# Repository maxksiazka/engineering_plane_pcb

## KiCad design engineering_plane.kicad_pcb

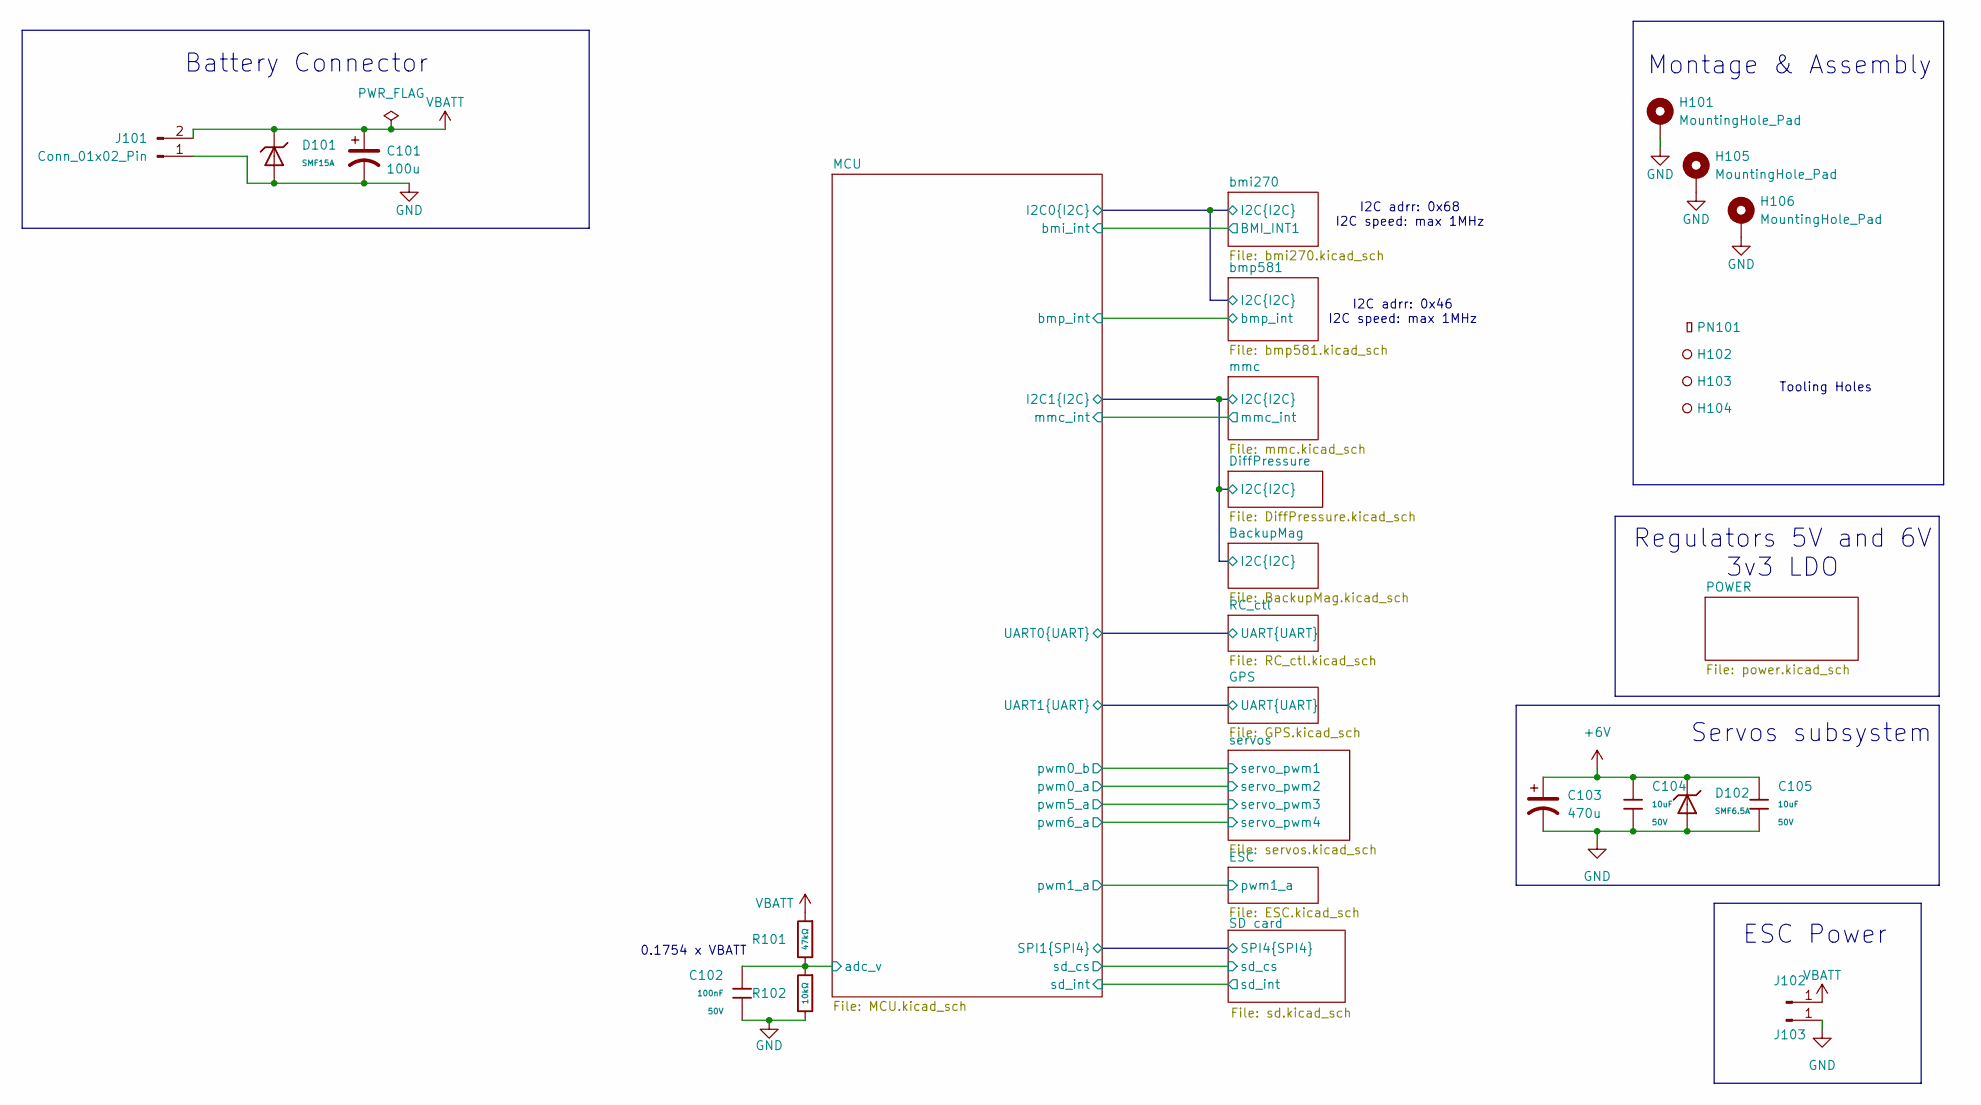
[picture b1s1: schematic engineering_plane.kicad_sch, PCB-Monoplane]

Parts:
C101: 100u; CP_Elec_6.3x7.7; Voltage 1kV; Tolerance 100%
C102: 100nF; C_0402; Voltage Rated 50V; Tolerance ±10%; Part CL05B104KB54PNC; LCSC C307331
C103: 470u; CP_Elec_10x10.5; Voltage 1kV; Tolerance 100%
C104, C105: 10uF; C_1206; Voltage Rated 50V; Tolerance ±10%; Part CL31A106KBHNNNE; LCSC C13585
D101: SMF15A; D_SOD-123FL; Clamping Voltage 24.4V; Voltage - Breakdown 16.7V; Part SMF15A; LCSC C19077509
D102: SMF6.5A; D_SOD-123FL; Clamping Voltage 11.2V; Voltage - Breakdown 7.98V; Part SMF6.5A; LCSC C41376089
H101, H105, H106: MountingHole_Pad; MountingHole_3.2mm_M3_Pad
H102, H103, H104: Hole_Tooling_JLCPCB
J101: Conn_01x02_Pin; AMASS_XT30PW-M_1x02_P2.50mm_Horizontal
J102, J103: Conn_01x01_Pin; SolderWire-2sqmm_1x01_D2mm_OD3.9mm
PN101: Part_Num_JLCPCB
R101: 47kΩ; R_0402; Overload Voltage (Max) 50V; Tolerance ±1%; Part 0402WGF4702TCE; LCSC C25792
R102: 10kΩ; R_0402; Overload Voltage (Max) 50V; Tolerance ±1%; Part 0402WGF1002TCE; LCSC C25744

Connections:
+6V: C103.1, C104.1, C105.1, D102.1; also elsewhere on the board
/MCU/adc_v: C102.1, R101.2, R102.1; also elsewhere on the board
GND: C101.2, C102.2, C103.2, C104.2, C105.2, D101.2, D102.2, H101.1 (1_1), H105.1 (1_1), H106.1 (1_1), J101.1, J103.1 (Pin_1_1), R102.2; also elsewhere on the board
VBATT: C101.1, D101.1, J101.2, J102.1 (Pin_1_1), R101.1; also elsewhere on the board

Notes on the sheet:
ESC Power
I2C adrr: 0x46 I2C speed: max 1MHz
Regulators 5V and 6V 3v3 LDO
0.1754 x VBATT
Tooling Holes
I2C adrr: 0x68 I2C speed: max 1MHz
Battery Connector
Montage & Assembly
Servos subsystem

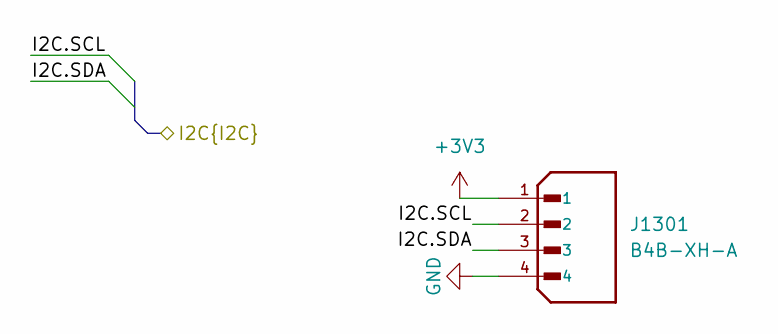
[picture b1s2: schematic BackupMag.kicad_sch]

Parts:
J1301: B4B-XH-A; JST_B4B-XH-A; PARTREV 7/4/21

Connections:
+3V3: J1301.1; also elsewhere on the board
/BackupMag/I2C.SCL: J1301.2; also elsewhere on the board
/BackupMag/I2C.SDA: J1301.3; also elsewhere on the board
GND: J1301.4; also elsewhere on the board

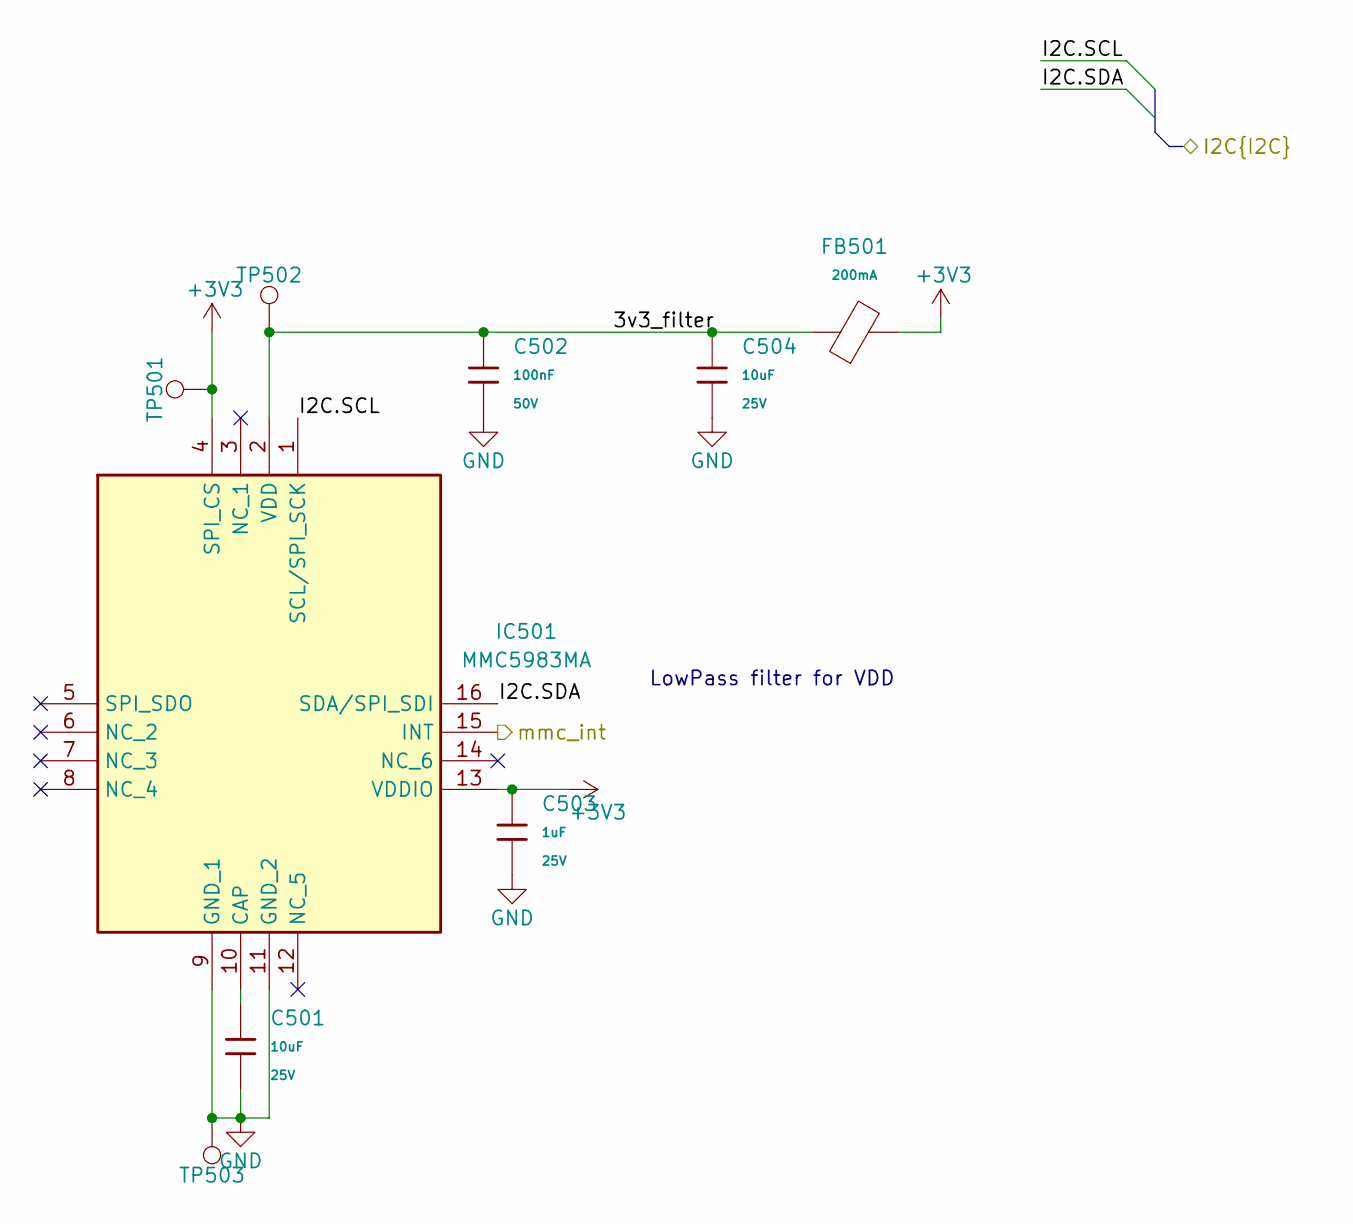
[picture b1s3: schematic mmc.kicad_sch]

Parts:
C501, C504: 10uF; C_0603; Voltage Rated 25V; Tolerance ±20%; Part CL10A106MA8NRNC; LCSC C96446
C502: 100nF; C_0402; Voltage Rated 50V; Tolerance ±10%; Part CL05B104KB54PNC; LCSC C307331
C503: 1uF; C_0402; Voltage Rated 25V; Tolerance ±10%; Part CL05A105KA5NQNC; LCSC C52923
FB501: FB_0603; Current Rating 200mA; Tolerance ±25%; Part GZ1608D601TF; LCSC C1002
IC501: MMC5983MA; Mouser Part Number 438-MMC5983MA
TP501, TP502, TP503: 1.0mm; TestPoint-1.0mm

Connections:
+3V3: C503.1, FB501.2, IC501.4 (SPI_CS), IC501.13 (VDDIO), TP501.1 (1_1); also elsewhere on the board
/BackupMag/I2C.SCL: IC501.1 (SCL/SPI_SCK); also elsewhere on the board
/BackupMag/I2C.SDA: IC501.16 (SDA/SPI_SDI); also elsewhere on the board
/MCU/mmc_int: IC501.15 (INT); also elsewhere on the board
/mmc/3v3_filter: C502.1, C504.1, FB501.1, IC501.2 (VDD), TP502.1 (1_1)
GND: C501.2, C502.2, C503.2, C504.2, IC501.9 (GND_1), IC501.11 (GND_2), TP503.1 (1_1); also elsewhere on the board
unnamed: C501.1, IC501.10 (CAP)

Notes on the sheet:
LowPass filter for VDD

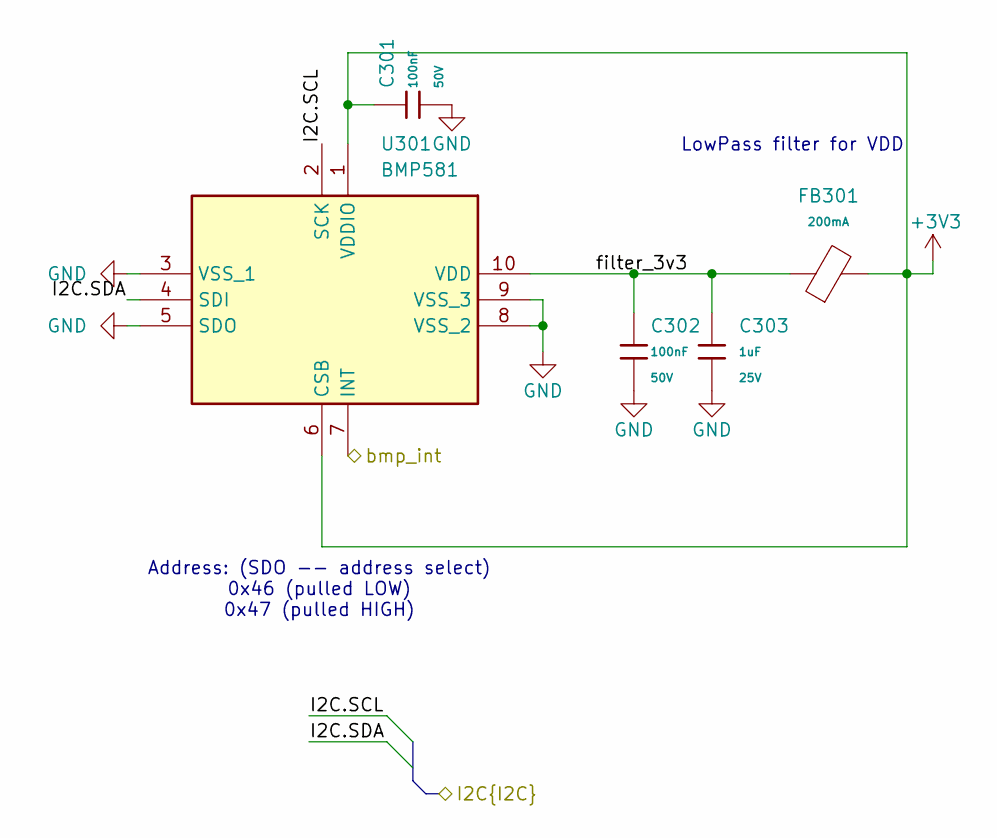
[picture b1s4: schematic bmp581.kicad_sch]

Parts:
C301, C302: 100nF; C_0402; Voltage Rated 50V; Tolerance ±10%; Part CL05B104KB54PNC; LCSC C307331
C303: 1uF; C_0402; Voltage Rated 25V; Tolerance ±10%; Part CL05A105KA5NQNC; LCSC C52923
FB301: FB_0603; Current Rating 200mA; Tolerance ±25%; Part GZ1608D601TF; LCSC C1002
U301: BMP581; Mouser Part Number 262-BMP581

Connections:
+3V3: C301.1, FB301.2, U301.1 (VDDIO), U301.6 (CSB); also elsewhere on the board
/MCU/I2C0.SCL: U301.2 (SCK); also elsewhere on the board
/MCU/I2C0.SDA: U301.4 (SDI); also elsewhere on the board
/MCU/bmp_int: U301.7 (INT); also elsewhere on the board
/bmp581/filter_3v3: C302.1, C303.1, FB301.1, U301.10 (VDD)
GND: C301.2, C302.2, C303.2, U301.3 (VSS_1), U301.5 (SDO), U301.8 (VSS_2), U301.9 (VSS_3); also elsewhere on the board

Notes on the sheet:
Address: (SDO -- address select) 0x46 (pulled LOW) 0x47 (pulled HIGH)
LowPass filter for VDD

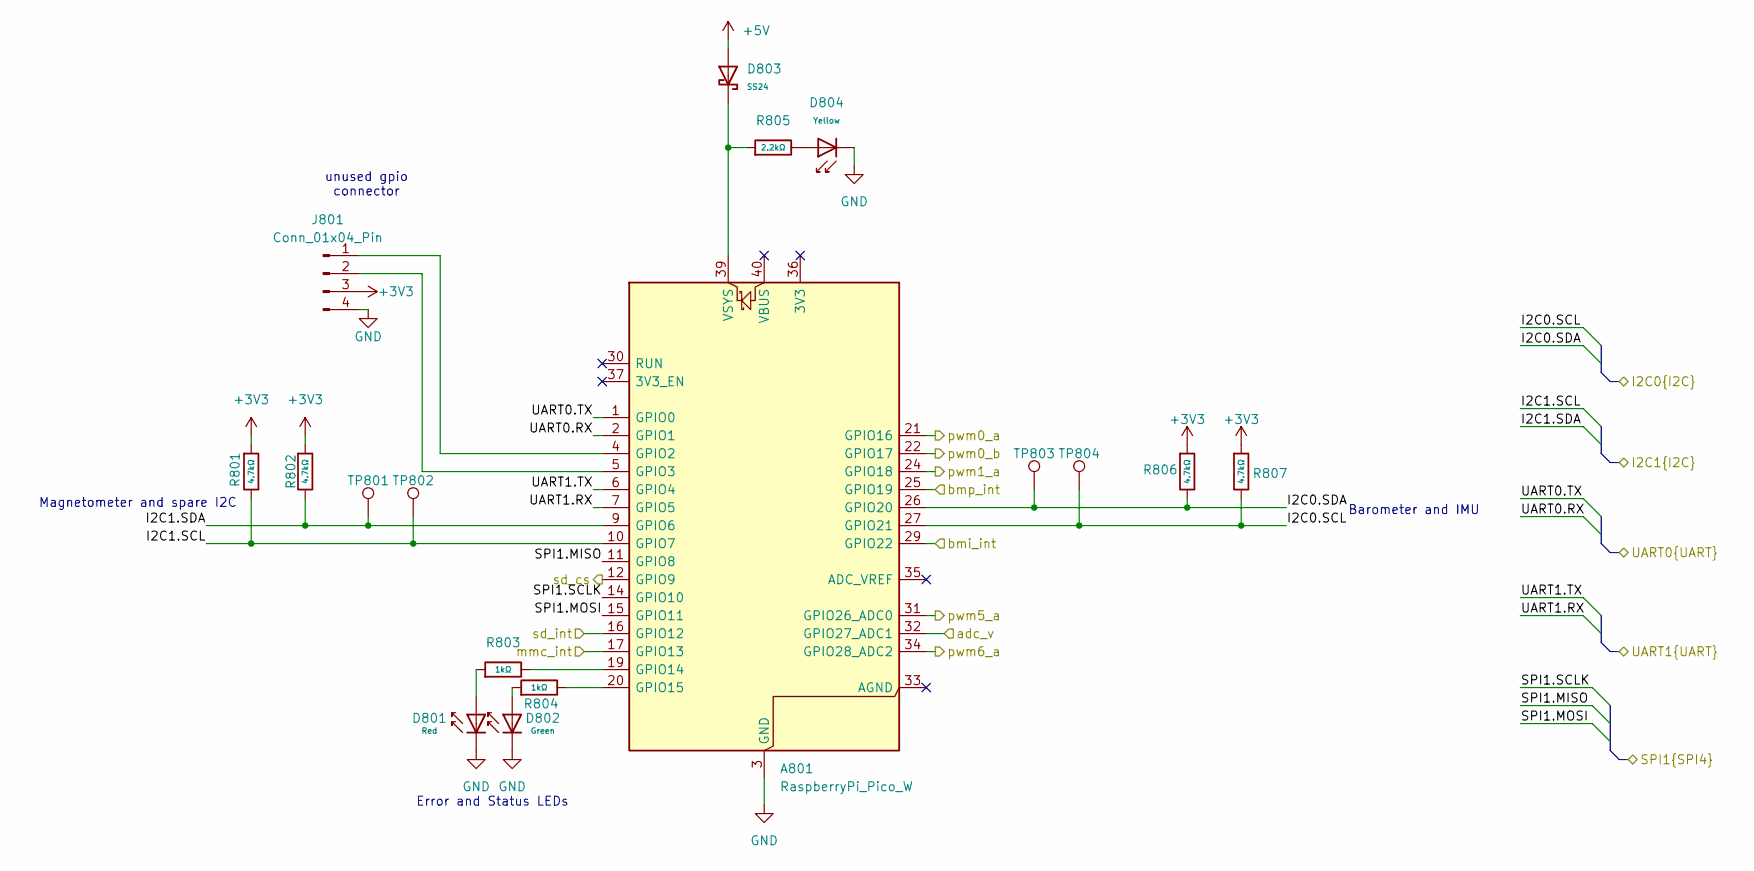
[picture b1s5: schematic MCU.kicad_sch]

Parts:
A801: RaspberryPi_Pico_W; RaspberryPi_Pico_Common_SMD
D801: Red; D_0805; Forward Voltage (VF) 1.6V~2.6V; Part NCD0805R1; LCSC C84256
D802: Green; D_0805; Part KT-0805G; LCSC C2297
D803: SS24; D_SMA; Forward Voltage (Vf@If) 0.55V@1.0A; Reverse Voltage (Vr) 40V; Part SS24; LCSC C7420362
D804: Yellow; D_0603; Forward Voltage (VF) 1.6V~2.6V; Part NCD0603Y2; LCSC C89811
J801: Conn_01x04_Pin; PinHeader_1x04_P2.54mm_Vertical
R801, R802, R806, R807: 4.7kΩ; R_0402; Overload Voltage (Max) 50V; Tolerance ±1%; Part 0402WGF4701TCE; LCSC C25900
R803, R804: 1kΩ; R_0402; Overload Voltage (Max) 50V; Tolerance ±1%; Part 0402WGF1001TCE; LCSC C11702
R805: 2.2kΩ; R_0402; Overload Voltage (Max) 50V; Tolerance ±1%; Part 0402WGF2201TCE; LCSC C25879
TP801, TP802, TP803, TP804: 1.0mm; TestPoint-1.0mm

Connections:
+3V3: J801.3, R801.1, R802.1, R806.1, R807.1; also elsewhere on the board
+5V: D803.2; also elsewhere on the board
/BackupMag/I2C.SCL: A801.10 (GPIO7), R801.2, TP802.1 (1_1); also elsewhere on the board
/BackupMag/I2C.SDA: A801.9 (GPIO6), R802.2, TP801.1 (1_1); also elsewhere on the board
/ESC/pwm1_a: A801.24 (GPIO18); also elsewhere on the board
/GPS/UART.RX: A801.7 (GPIO5); also elsewhere on the board
/GPS/UART.TX: A801.6 (GPIO4); also elsewhere on the board
/MCU/I2C0.SCL: A801.27 (GPIO21), R807.2, TP804.1 (1_1); also elsewhere on the board
/MCU/I2C0.SDA: A801.26 (GPIO20), R806.2, TP803.1 (1_1); also elsewhere on the board
/MCU/SPI1.MISO: A801.11 (GPIO8); also elsewhere on the board
/MCU/SPI1.MOSI: A801.15 (GPIO11); also elsewhere on the board
/MCU/SPI1.SCLK: A801.14 (GPIO10); also elsewhere on the board
/MCU/UART0.RX: A801.2 (GPIO1); also elsewhere on the board
/MCU/UART0.TX: A801.1 (GPIO0); also elsewhere on the board
/MCU/adc_v: A801.32 (GPIO27_ADC1); also elsewhere on the board
/MCU/bmi_int: A801.29 (GPIO22); also elsewhere on the board
/MCU/bmp_int: A801.25 (GPIO19); also elsewhere on the board
/MCU/mmc_int: A801.17 (GPIO13); also elsewhere on the board
/MCU/pwm0_a: A801.21 (GPIO16); also elsewhere on the board
/MCU/pwm0_b: A801.22 (GPIO17); also elsewhere on the board
/MCU/pwm5_a: A801.31 (GPIO26_ADC0); also elsewhere on the board
/MCU/pwm6_a: A801.34 (GPIO28_ADC2); also elsewhere on the board
/MCU/sd_cs: A801.12 (GPIO9); also elsewhere on the board
/MCU/sd_int: A801.16 (GPIO12); also elsewhere on the board
GND: A801.3 (GND), A801.8 (GND), A801.13 (GND), A801.18 (GND), A801.23 (GND), A801.28 (GND), A801.38 (GND), D801.1, D802.1, D804.1, J801.4; also elsewhere on the board
unnamed: A801.4 (GPIO2), J801.1
unnamed: A801.5 (GPIO3), J801.2
unnamed: A801.19 (GPIO14), R803.2
unnamed: A801.20 (GPIO15), R804.2
unnamed: A801.39 (VSYS), D803.1, R805.1
unnamed: D801.2, R803.1
unnamed: D802.2, R804.1
unnamed: D804.2, R805.2

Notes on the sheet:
Error and Status LEDs
Magnetometer and spare I2C
unused gpio connector
Barometer and IMU

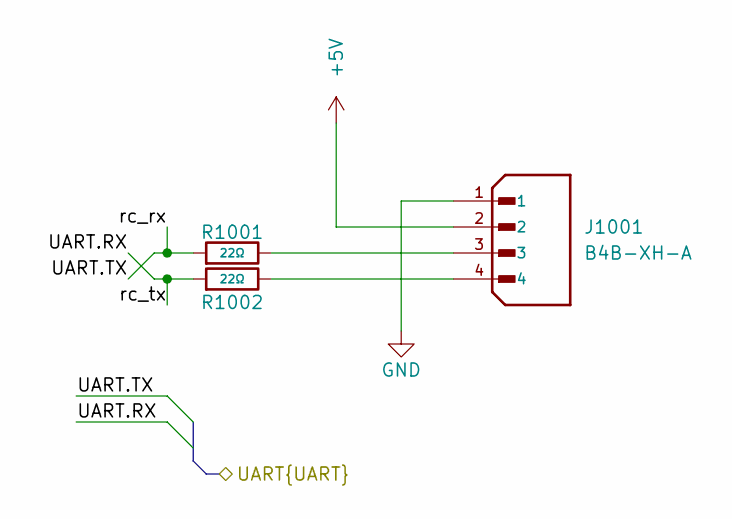
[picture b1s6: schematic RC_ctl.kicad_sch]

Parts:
J1001: B4B-XH-A; JST_B4B-XH-A; PARTREV 7/4/21
R1001, R1002: 22Ω; R_0603; Overload Voltage (Max) 75V; Tolerance ±1%; Part 0603WAF220JT5E; LCSC C23345

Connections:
+5V: J1001.2; also elsewhere on the board
/MCU/UART0.RX: R1002.1; also elsewhere on the board
/MCU/UART0.TX: R1001.1; also elsewhere on the board
GND: J1001.1; also elsewhere on the board
unnamed: J1001.3, R1001.2
unnamed: J1001.4, R1002.2

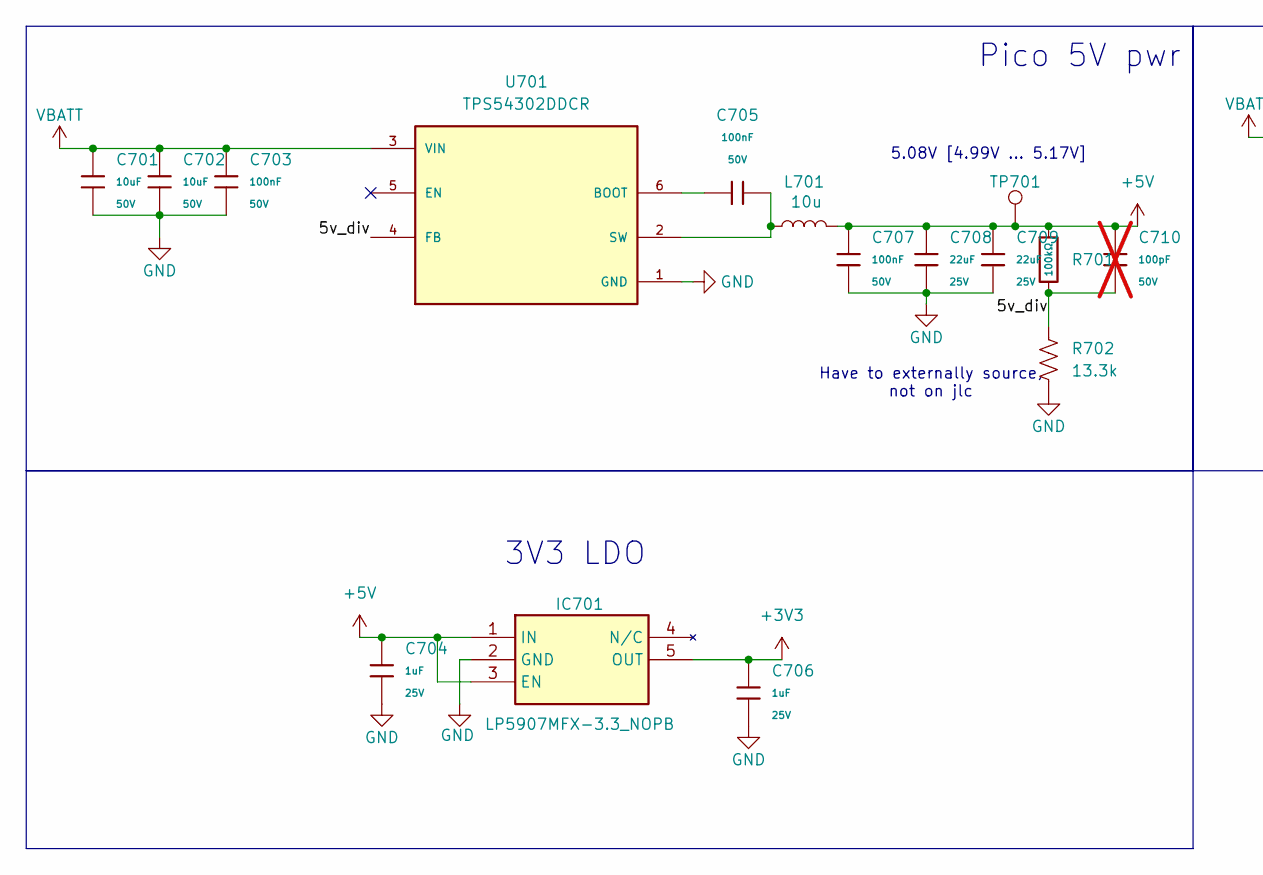
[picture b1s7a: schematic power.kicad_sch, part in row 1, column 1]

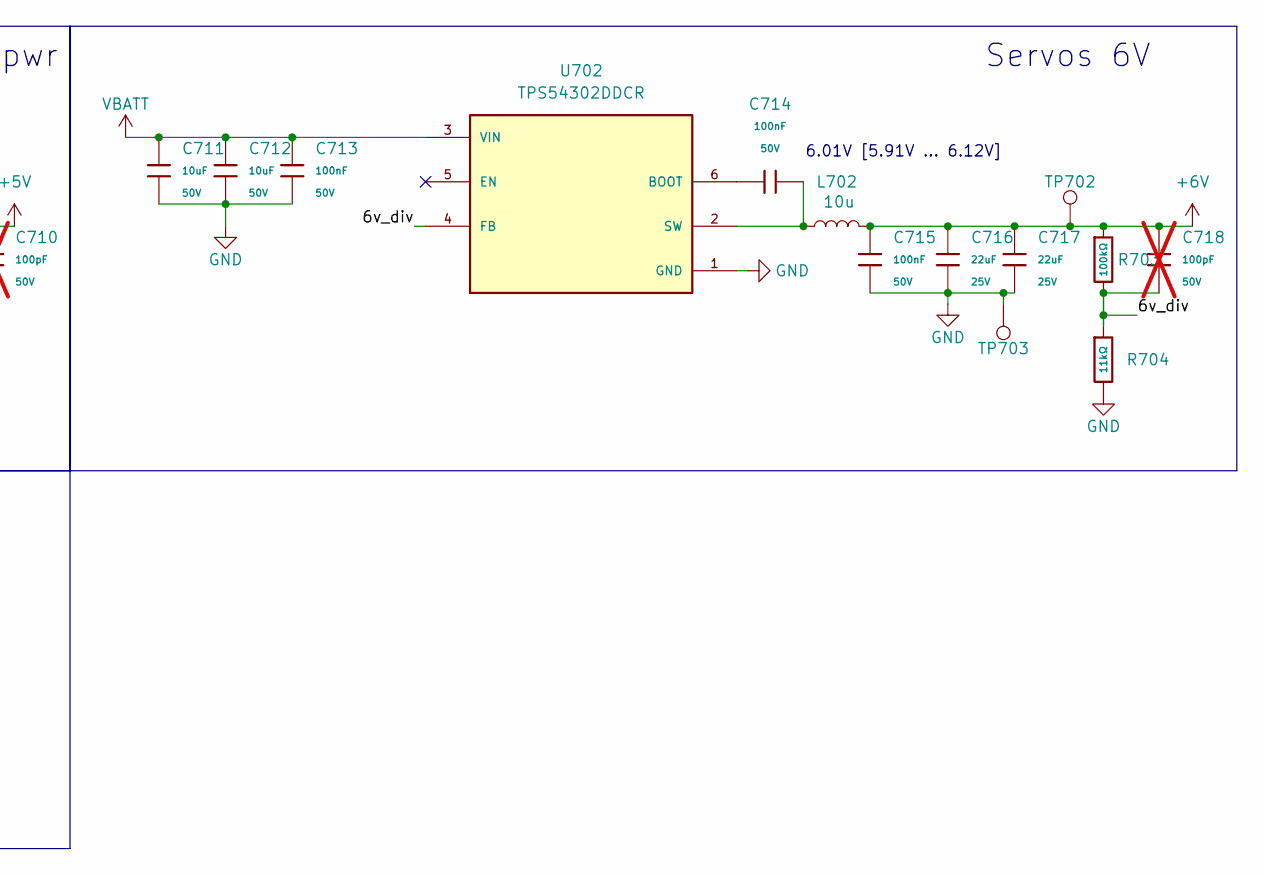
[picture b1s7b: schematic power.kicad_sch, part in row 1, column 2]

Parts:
C701, C702, C711, C712: 10uF; C_1206; Voltage Rated 50V; Tolerance ±10%; Part CL31A106KBHNNNE; LCSC C13585
C703, C705, C707, C713, C715: 100nF; C_0603; Voltage Rated 50V; Tolerance ±10%; Part CC0603KRX7R9BB104; LCSC C14663
C704, C706: 1uF; C_0402; Voltage Rated 25V; Tolerance ±10%; Part CL05A105KA5NQNC; LCSC C52923
C708, C709, C716, C717: 22uF; C_1206; Voltage Rated 25V; Tolerance ±10%; Part CL31A226KAHNNNE; LCSC C12891
C710, C718: 100pF; C_0603; Voltage Rated 50V; Tolerance ±5%; Part CL10C101JB8NNNC; LCSC C14858; not fitted
C714: 100nF; C_0402; Voltage Rated 50V; Tolerance ±10%; Part CL05B104KB54PNC; LCSC C307331
IC701: LP5907MFX-3.3_NOPB; SOT95P280X145-5M; Mouser Part Number 595-LP5907MFX-3.3NPB
L701: 10u; L_7.3x7.3_H4.5
L702: 10u; 7447714220
R701, R703: 100kΩ; R_0603; Overload Voltage (Max) 75V; Tolerance ±1%; Part 0603WAF1003T5E; LCSC C25803
R702: 13.3k; R_0603_1608Metric
R704: 11kΩ; R_0603; Overload Voltage (Max) 75V; Tolerance ±1%; Part 0603WAF1102T5E; LCSC C25950
TP701, TP702, TP703: 1.0mm; TestPoint-1.0mm
U701, U702: TPS54302DDCR; SOT95P280X110-6N; PARTREV A

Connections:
+3V3: C706.1, IC701.5 (OUT); also elsewhere on the board
+5V: C704.1, C707.1, C708.1, C709.1, C710.1, IC701.1 (IN), IC701.3 (EN), L701.2, R701.1, TP701.1 (1_1); also elsewhere on the board
+6V: C715.1, C716.1, C717.1, C718.1, L702.2, R703.1, TP702.1 (1_1); also elsewhere on the board
/POWER/5v_div: C710.2, R701.2, R702.2, U701.4 (FB)
/POWER/6v_div: C718.2, R703.2, R704.1, U702.4 (FB)
GND: C701.2, C702.2, C703.2, C704.2, C706.2, C707.2, C708.2, C709.2, C711.2, C712.2, C713.2, C715.2, C716.2, C717.2, IC701.2 (GND), R702.1, R704.2, TP703.1 (1_1), U701.1 (GND), U702.1 (GND); also elsewhere on the board
unnamed: C705.1, U701.6 (BOOT)
unnamed: C705.2, L701.1, U701.2 (SW)
unnamed: C714.1, U702.6 (BOOT)
unnamed: C714.2, L702.1, U702.2 (SW)
VBATT: C701.1, C702.1, C703.1, C711.1, C712.1, C713.1, U701.3 (VIN), U702.3 (VIN); also elsewhere on the board

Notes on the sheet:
5.08V [4.99V ... 5.17V]
Have to externally source, not on jlc
Servos 6V
Pico 5V pwr
3V3 LDO
6.01V [5.91V ... 6.12V]

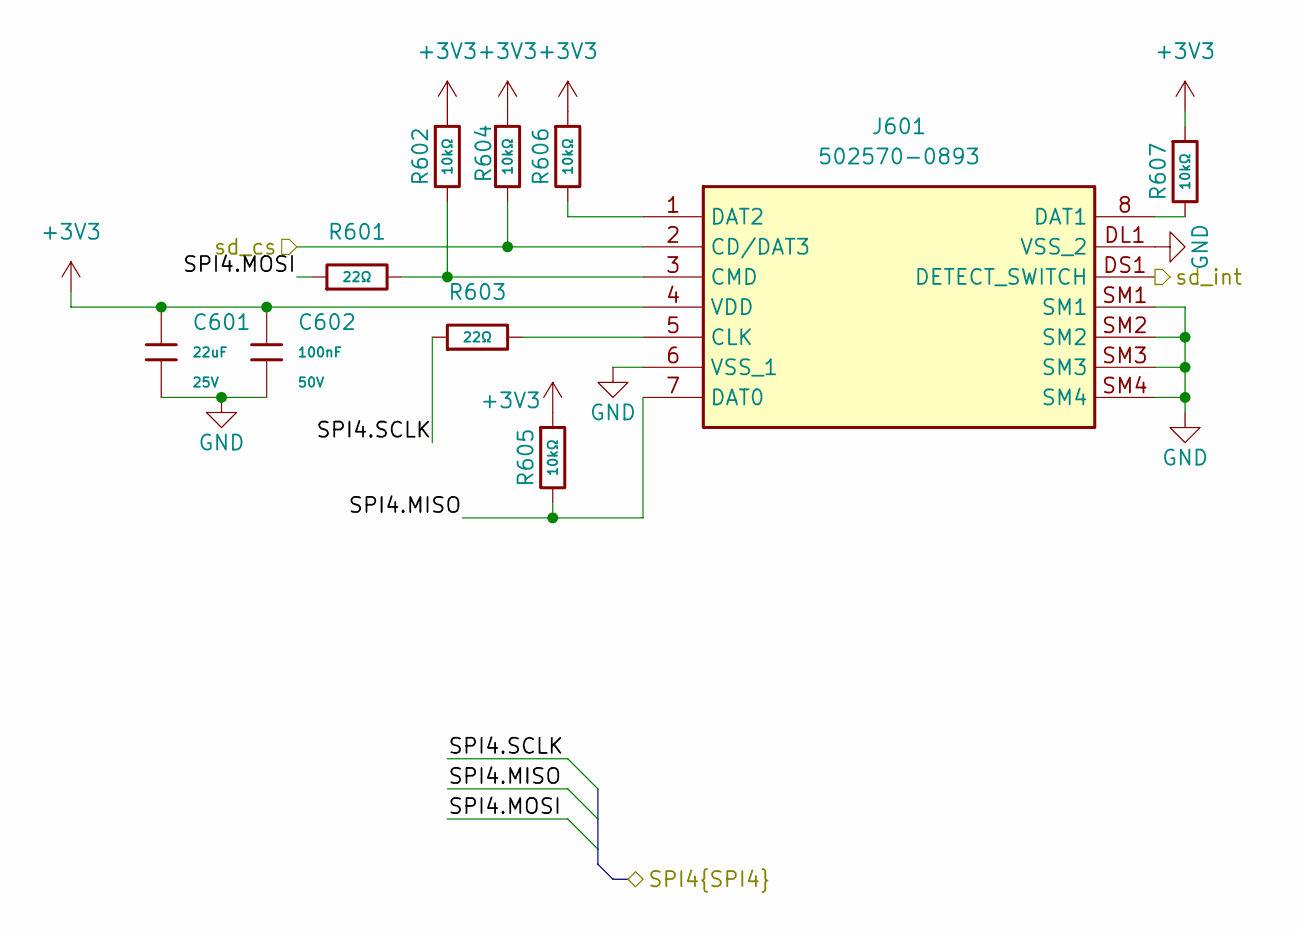
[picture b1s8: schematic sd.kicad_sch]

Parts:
C601: 22uF; C_1206; Voltage Rated 25V; Tolerance ±10%; Part CL31A226KAHNNNE; LCSC C12891
C602: 100nF; C_0402; Voltage Rated 50V; Tolerance ±10%; Part CL05B104KB54PNC; LCSC C307331
J601: 502570-0893; 5025700893; Mouser Part Number 538-502570-0893
R601, R603: 22Ω; R_0402; Overload Voltage (Max) 50V; Tolerance ±1%; Part 0402WGF220JTCE; LCSC C25092
R602, R604, R605, R606, R607: 10kΩ; R_0402; Overload Voltage (Max) 50V; Tolerance ±1%; Part 0402WGF1002TCE; LCSC C25744

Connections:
+3V3: C601.1, C602.1, J601.4 (VDD), R602.1, R604.1, R605.1, R606.1, R607.1; also elsewhere on the board
/MCU/SPI1.MISO: J601.7 (DAT0), R605.2; also elsewhere on the board
/MCU/SPI1.MOSI: R601.1; also elsewhere on the board
/MCU/SPI1.SCLK: R603.1; also elsewhere on the board
/MCU/sd_cs: J601.2 (CD/DAT3), R604.2; also elsewhere on the board
/MCU/sd_int: J601.DS1 (DETECT_SWITCH); also elsewhere on the board
GND: C601.2, C602.2, J601.6 (VSS_1), J601.DL1 (VSS_2), J601.SM1, J601.SM2, J601.SM3, J601.SM4; also elsewhere on the board
unnamed: J601.5 (CLK), R603.2
unnamed: J601.3 (CMD), R601.2, R602.2
unnamed: J601.8 (DAT1), R607.2
unnamed: J601.1 (DAT2), R606.2

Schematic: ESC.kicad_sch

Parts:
J1101: B3B-XH-A__LF__SN_; JST_B3B-XH-A__LF__SN_; PARTREV 7/4/21
R1101: 10kΩ; R_0402; Overload Voltage (Max) 50V; Tolerance ±1%; Part 0402WGF1002TCE; LCSC C25744
R1102: 22Ω; R_0402; Overload Voltage (Max) 50V; Tolerance ±1%; Part 0402WGF220JTCE; LCSC C25092

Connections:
/ESC/pwm1_a: R1102.2; also elsewhere on the board
GND: J1101.1, R1101.2; also elsewhere on the board
unnamed: J1101.3, R1101.1, R1102.1

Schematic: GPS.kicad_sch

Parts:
J901: B4B-XH-A; JST_B4B-XH-A; PARTREV 7/4/21
R901, R902: 22Ω; R_0603; Overload Voltage (Max) 75V; Tolerance ±1%; Part 0603WAF220JT5E; LCSC C23345

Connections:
+3V3: J901.1; also elsewhere on the board
/GPS/UART.RX: R902.1; also elsewhere on the board
/GPS/UART.TX: R901.1; also elsewhere on the board
GND: J901.4; also elsewhere on the board
unnamed: J901.2, R901.2
unnamed: J901.3, R902.2

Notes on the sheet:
Place in Poka-Yoke

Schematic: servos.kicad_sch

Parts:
J401, J402, J403, J404: S3B-XH-A-1__LF__SN_; S3BXHA1LFSN; Manufacturer_Part_Number S3B-XH-A-1 (LF)(SN)
R401, R402, R403, R404: 22Ω; R_0402; Overload Voltage (Max) 50V; Tolerance ±1%; Part 0402WGF220JTCE; LCSC C25092
R405, R406, R407, R408: 10kΩ; R_0402; Overload Voltage (Max) 50V; Tolerance ±1%; Part 0402WGF1002TCE; LCSC C25744

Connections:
+6V: J401.2, J402.2, J403.2, J404.2; also elsewhere on the board
/MCU/pwm0_a: R402.1; also elsewhere on the board
/MCU/pwm0_b: R401.1; also elsewhere on the board
/MCU/pwm5_a: R403.1; also elsewhere on the board
/MCU/pwm6_a: R404.1; also elsewhere on the board
GND: J401.1, J402.1, J403.1, J404.1, R405.2, R406.2, R407.2, R408.2; also elsewhere on the board
unnamed: J401.3, R401.2, R405.1
unnamed: J402.3, R402.2, R406.1
unnamed: J403.3, R403.2, R407.1
unnamed: J404.3, R404.2, R408.1

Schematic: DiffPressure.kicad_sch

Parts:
J1201: B4B-XH-A; JST_B4B-XH-A; PARTREV 7/4/21

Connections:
+5V: J1201.1; also elsewhere on the board
/BackupMag/I2C.SCL: J1201.2; also elsewhere on the board
/BackupMag/I2C.SDA: J1201.3; also elsewhere on the board
GND: J1201.4; also elsewhere on the board

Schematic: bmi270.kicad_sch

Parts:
C201, C202: 100nF; C_0402; Voltage Rated 50V; Tolerance ±10%; Part CL05B104KB54PNC; LCSC C307331
C203: 1uF; C_0402; Voltage Rated 25V; Tolerance ±10%; Part CL05A105KA5NQNC; LCSC C52923
FB201: FB_0603; Current Rating 200mA; Tolerance ±25%; Part GZ1608D601TF; LCSC C1002
IC201: BMI270; Mouser Part Number 262-BMI270
TP201, TP202: 1.0mm; TestPoint-1.0mm

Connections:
+3V3: C201.1, FB201.2, IC201.5 (VDDIO), IC201.12 (CSB), TP201.1 (1_1); also elsewhere on the board
/MCU/I2C0.SCL: IC201.13 (SCX); also elsewhere on the board
/MCU/I2C0.SDA: IC201.14 (SDX); also elsewhere on the board
/MCU/bmi_int: IC201.4 (INT1); also elsewhere on the board
/bmi270/filter_3v3: C202.1, C203.1, FB201.1, IC201.8 (VDD), TP202.1 (1_1)
GND: C201.2, C202.2, C203.2, IC201.1 (SDO), IC201.6 (GNDIO), IC201.7 (GND); also elsewhere on the board

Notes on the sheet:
Address: 0x68 (pulled LOW) 0x69 (pulled to VDDIO)
LowPass filter for VDD

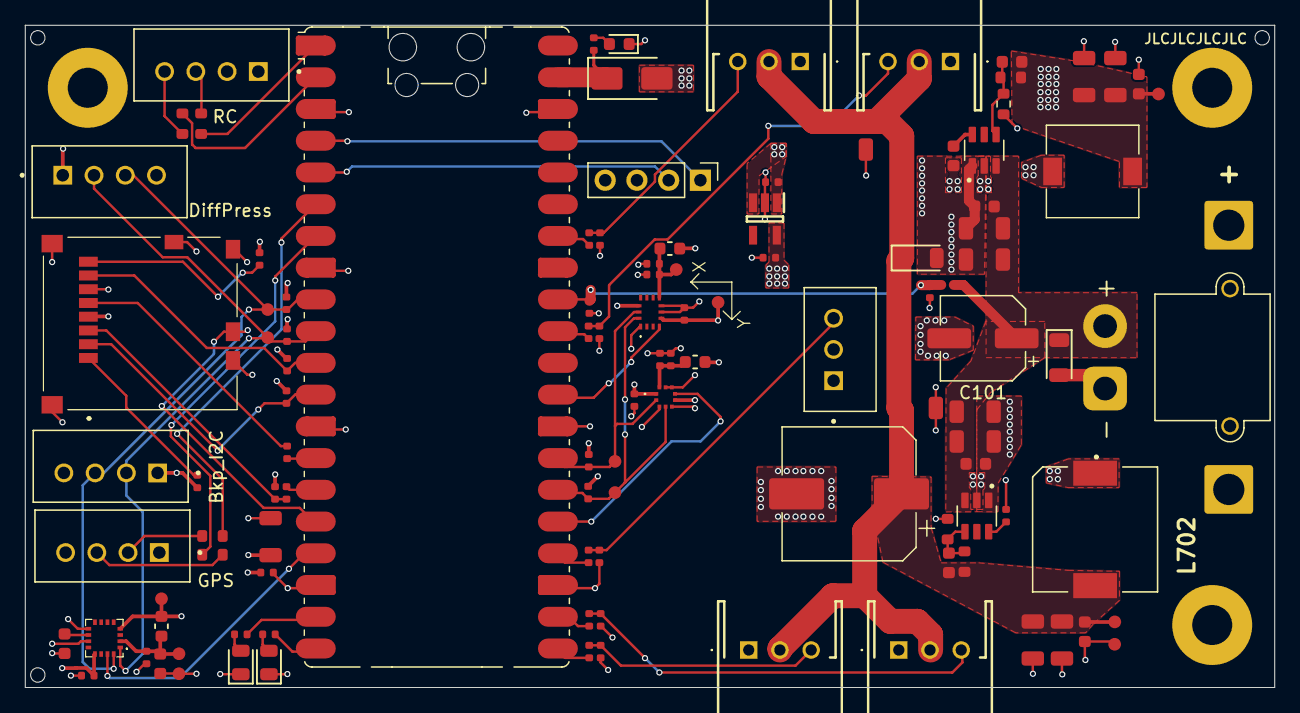
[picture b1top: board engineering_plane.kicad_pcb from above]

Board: 4 copper layers, 100.0 x 53.0 mm, 120 parts (0 on the bottom side), 58 nets.

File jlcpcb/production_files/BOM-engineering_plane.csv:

Comment,Designator,Footprint,LCSC,Quantity
100kΩ,"R701,R703",R_0603,C25803,2
100nF,"C703,C705,C707,C713,C715",C_0603,C14663,5
100nF,"C102,C201,C202,C301,C302,C502,C602,C714",C_0402,C307331,8
10kΩ,"R102,R1101,R405,R406,R407,R408,R602,R604,R605,R606,R607",R_0402,C25744,11
10uF,"C104,C105,C701,C702,C711,C712",C_1206,C13585,6
10uF,"C501,C504",C_0603,C96446,2
11kΩ,R704,R_0603,C25950,1
1kΩ,"R803,R804",R_0402,C11702,2
1uF,"C203,C303,C503,C704,C706",C_0402,C52923,5
2.2kΩ,R805,R_0402,C25879,1
22uF,"C601,C708,C709,C716,C717",C_1206,C12891,5
22Ω,"R1001,R1002,R901,R902",R_0603,C23345,4
22Ω,"R1102,R401,R402,R403,R404,R601,R603",R_0402,C25092,7
4.7kΩ,"R801,R802,R806,R807",R_0402,C25900,4
47kΩ,R101,R_0402,C25792,1
Green,D802,D_0805,C2297,1
Red,D801,D_0805,C84256,1
SMF15A,D101,D_SOD-123FL,C19077509,1
SMF6.5A,D102,D_SOD-123FL,C41376089,1
SS24,D803,D_SMA,C7420362,1
Yellow,D804,D_0603,C89811,1
~,"FB201,FB301,FB501",FB_0603,C1002,3
BMP581,U301,BMP581,,1
BMI270,IC201,BMI270,,1
TPS54302DDCR,U702,SOT95P280X110-6N,,1
TPS54302DDCR,U701,SOT95P280X110-6N,,1
MMC5983MA,IC501,MMC5983MA,,1
13.3k,R702,R_0603_1608Metric,,1
